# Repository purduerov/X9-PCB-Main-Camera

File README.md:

# X9-PCB-Main-Camera
Has Main Camera, Lights and Lasers for sight

## TODO:
- [X] Make the traces D_M and D_P the same length.  Use the command "run length" to determine the length of each trace.
- [X] Shorten the D_M and D_P traces so that they go to the right and then down.  You have them going right then down then up.
- [X] Have Charles and/or I(Luke) look over your schematic.  Some of the connections to parts don't seem to be correct.
- [X] Swap some of the connections for the board to binder connector.  Swap "PWN" and +3.3V.  Not sure if you now this, but the correct name is PWM (pulse width modulaton).
- [X] Talk to Alex Ruffino in order to figure out the hole placement in order to mount the servo.
- [X] Make sure with Alex that we are making the board properlly so that we can mount the 3D printed laser mounting cones on the board.
- [X] Move the laser voltage trace out of the way of the hole that is going to be in the the middle of the board, because the camera needs to go through there

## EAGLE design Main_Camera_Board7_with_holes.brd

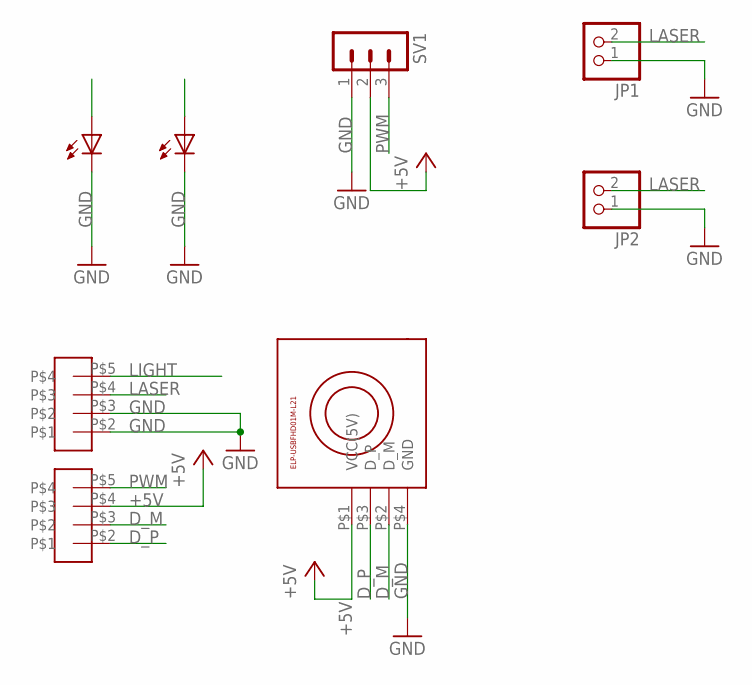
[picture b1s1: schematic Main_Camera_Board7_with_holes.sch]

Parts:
JP1, JP2: PINHD-1X2; 1X02
SV1: MA03-1
U$1: ELP-USBFHD01M-L21
U$2, U$3: LED
U$4, U$5: T21; T2I

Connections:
+5V: SV1.2, U$1.P$1 (VCC(5V)), U$5.P$4
D_M: U$1.P$2 (D_M), U$5.P$3
D_P: U$1.P$3 (D_P), U$5.P$2
GND: JP1.1, JP2.1, SV1.1, U$1.P$4 (GND), U$2.P$1 (CATHODE), U$2.P$3 (CATHODE), U$3.P$1 (CATHODE), U$3.P$3 (CATHODE), U$4.P$2, U$4.P$3
LASER: JP1.2, JP2.2, U$4.P$4
LIGHT: U$2.P$2 (ANODE), U$3.P$2 (ANODE), U$4.P$5
PWM: SV1.3, U$5.P$5

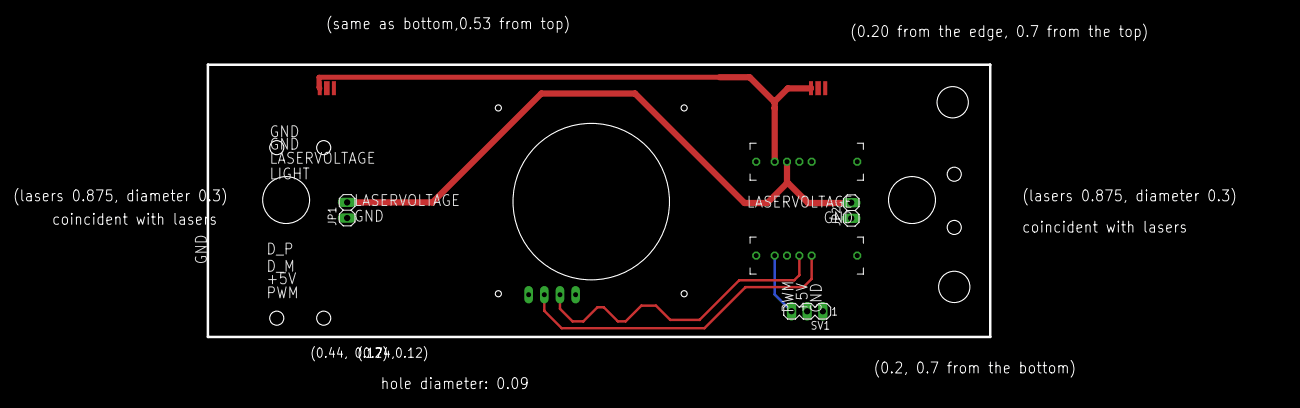
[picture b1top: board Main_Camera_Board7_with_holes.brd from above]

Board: 2 copper layers, 127.0 x 44.2 mm, 8 parts (0 on the bottom side), 7 nets.

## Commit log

2016-10-29 Started Work on Camera Board
2016-10-29 put leds in correct positions
2016-11-02 OutputJob
2016-11-03 more updates
2016-11-03 Added TODO list
2016-11-04 made a few changes to camera board
2016-11-04 Fixed schematic errors
2016-11-08 added some things to TODO list
2016-11-08 wait one more thing
2016-11-09 Add todo to the readme
2016-11-09 Deleted the todo
2016-11-09 Added Instructions for Holes
2016-11-11 Created board with holes for mounting
2016-11-17 fixed airwire+updated readme
2016-11-18 Revert "Added Instructions for Holes"
    This reverts commit acebc77281901a6f31d99e6ed7f09fe10f3c712a.
2016-11-18 made central camera hole larger, readjusted traces, fixed drc issues
2016-11-18 removed holes
2016-11-21 added luke made changes, moved connectors
2016-11-21 added holes to feed the wires down
2016-12-10 Removed random boards
2016-12-18 Fixed problem with all files being deleted
2016-12-18 Fixed problem with gitignore
2016-12-23 edited the silk screen
